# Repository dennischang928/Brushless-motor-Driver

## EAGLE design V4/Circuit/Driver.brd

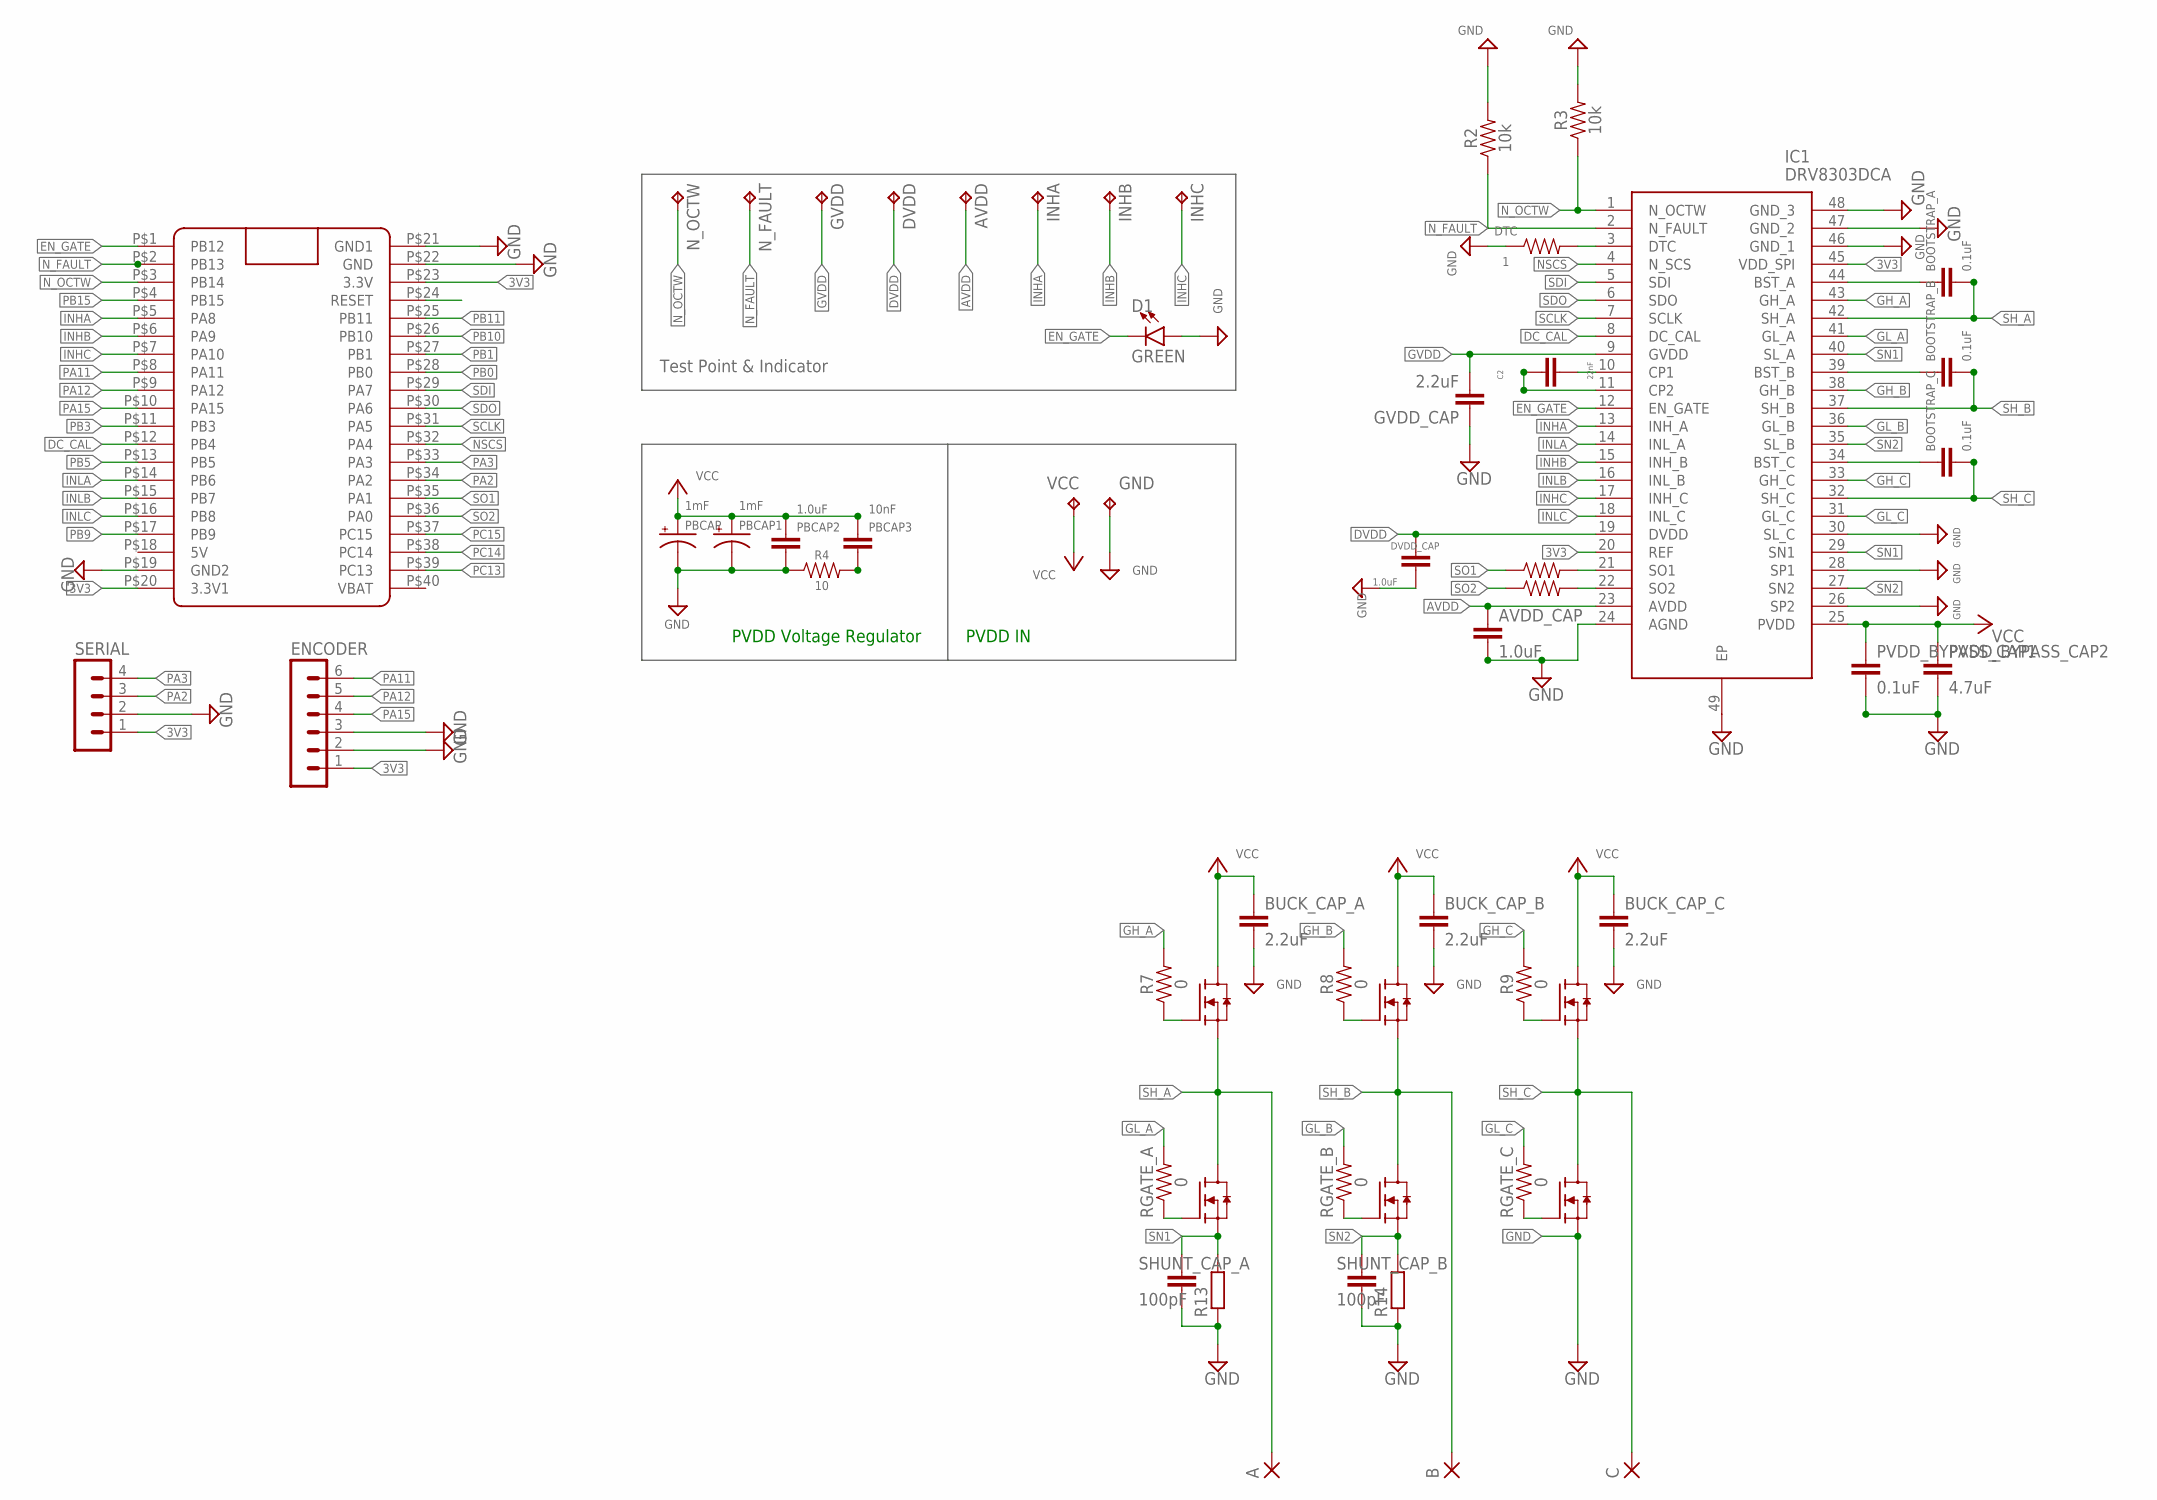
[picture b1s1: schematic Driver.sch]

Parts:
A: SMD5; SMD2,54-5,08
AVDD: TPTP16R; TP16R
AVDD_CAP: 1.0uF; 0603
B: SMD5; SMD2,54-5,08
BOOTSTRAP_A: 0.1uF; 0603
BOOTSTRAP_B: 0.1uF; 0603
BOOTSTRAP_C: 0.1uF; 0603
BUCK_CAP_A: 2.2uF; 0603
BUCK_CAP_B: 2.2uF; 0603
BUCK_CAP_C: 2.2uF; 0603
C: SMD5; SMD2,54-5,08
C2: 22nF; 0603
D1: GREEN; LED-0603
DTC: 1; 0603
DVDD: TPTP16R; TP16R
DVDD_CAP: 1.0uF; 0603
ENCODER: MA06-1
GND: TPPAD1-20Y; P1-20Y
GVDD: TPTP16R; TP16R
GVDD_CAP: 2.2uF; 0603
HA: IRLR7843; TO252
HB: IRLR7843; TO252
HC: IRLR7843; TO252
IC1: DRV8303DCA; SOP50P810X120-49N
INHA: TPTP16R; TP16R
INHB: TPTP16R; TP16R
INHC: TPTP16R; TP16R
LA: IRLR7843; TO252
LB: IRLR7843; TO252
LC: IRLR7843; TO252
N_FAULT: TPTP16R; TP16R
N_OCTW: TPTP16R; TP16R
PBCAP, PBCAP1: 1mF; CPOL-RADIAL-5MM-10MM
PBCAP2: 1.0uF; 0603
PBCAP3: 10nF; 0603
PVDD_BYPASS_CAP1: 0.1uF; 0603
PVDD_BYPASS_CAP2: 4.7uF; 0603
R2, R3: 10k; 0603
R4: 10; 0603
R5, R6: 47; 0603
R7, R8, R9: 0; 0603
R13, R14: R-EU_R2512; R2512
RGATE_A: 0; 0603
RGATE_B: 0; 0603
RGATE_C: 0; 0603
SERIAL: MA04-1
SHUNT_CAP_A: 100pF; 0603
SHUNT_CAP_B: 100pF; 0603
U$1: BLUE_PILLADVANCED; BLUE_PILL_ADV
VCC: TPPAD1-20Y; P1-20Y

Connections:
3V3: ENCODER.1, IC1.20 (REF), IC1.45 (VDD_SPI), SERIAL.1, U$1.P$20 (3.3V1), U$1.P$23 (3.3V)
AVDD: AVDD.TP, AVDD_CAP.1, IC1.23 (AVDD)
DC_CAL: IC1.8 (DC_CAL), U$1.P$12 (PB4)
DVDD: DVDD.TP, DVDD_CAP.1, IC1.19 (DVDD)
EN_GATE: D1.C, IC1.12 (EN_GATE), U$1.P$1 (PB12)
GH_A: IC1.43 (GH_A), R7.2
GH_B: IC1.38 (GH_B), R8.2
GH_C: IC1.33 (GH_C), R9.2
GL_A: IC1.41 (GL_A), RGATE_A.2
GL_B: IC1.36 (GL_B), RGATE_B.2
GL_C: IC1.31 (GL_C), RGATE_C.2
GND: AVDD_CAP.2, BUCK_CAP_A.2, BUCK_CAP_B.2, BUCK_CAP_C.2, D1.A, DTC.1, DVDD_CAP.2, ENCODER.2, ENCODER.3, GND.TP, GVDD_CAP.1, IC1.24 (AGND), IC1.26 (SP2), IC1.28 (SP1), IC1.30 (SL_C), IC1.46 (GND_1), IC1.47 (GND_2), IC1.48 (GND_3), IC1.49 (EP), LC.2 (S), PBCAP.-, PBCAP1.-, PBCAP2.2, PVDD_BYPASS_CAP1.2, PVDD_BYPASS_CAP2.2, R2.2, R3.2, R4.1, R13.1, R14.1, SERIAL.2, SHUNT_CAP_A.2, SHUNT_CAP_B.2, U$1.P$19 (GND2), U$1.P$21 (GND1), U$1.P$22 (GND)
GVDD: GVDD.TP, GVDD_CAP.2, IC1.9 (GVDD)
INHA: IC1.13 (INH_A), INHA.TP, U$1.P$5 (PA8)
INHB: IC1.15 (INH_B), INHB.TP, U$1.P$6 (PA9)
INHC: IC1.17 (INH_C), INHC.TP, U$1.P$7 (PA10)
INLA: IC1.14 (INL_A), U$1.P$14 (PB6)
INLB: IC1.16 (INL_B), U$1.P$15 (PB7)
INLC: IC1.18 (INL_C), U$1.P$16 (PB8)
unnamed: DTC.2, IC1.3 (DTC)
unnamed: PBCAP3.2, R4.2
unnamed: BOOTSTRAP_A.1, IC1.44 (BST_A)
unnamed: HA.1 (G), R7.1
unnamed: HB.1 (G), R8.1
unnamed: HC.1 (G), R9.1
unnamed: BOOTSTRAP_B.1, IC1.39 (BST_B)
unnamed: LC.1 (G), RGATE_C.1
unnamed: BOOTSTRAP_C.1, IC1.34 (BST_C)
unnamed: LB.1 (G), RGATE_B.1
unnamed: LA.1 (G), RGATE_A.1
unnamed: C2.2, IC1.10 (CP1)
unnamed: C2.1, IC1.11 (CP2)
NSCS: IC1.4 (N_SCS), U$1.P$32 (PA4)
N_FAULT: IC1.2 (N_FAULT), N_FAULT.TP, R2.1, U$1.P$2 (PB13)
N_OCTW: IC1.1 (N_OCTW), N_OCTW.TP, R3.1, U$1.P$3 (PB14)
PA2: SERIAL.3, U$1.P$34 (PA2)
PA3: SERIAL.4, U$1.P$33 (PA3)
PA11: ENCODER.6, U$1.P$8 (PA11)
PA12: ENCODER.5, U$1.P$9 (PA12)
PA15: ENCODER.4, U$1.P$10 (PA15)
PB0: U$1.P$28 (PB0)
PB1: U$1.P$27 (PB1)
PB3: U$1.P$11 (PB3)
PB5: U$1.P$13 (PB5)
PB9: U$1.P$17 (PB9)
PB10: U$1.P$26 (PB10)
PB11: U$1.P$25 (PB11)
PB15: U$1.P$4 (PB15)
PC13: U$1.P$39 (PC13)
PC14: U$1.P$38 (PC14)
PC15: U$1.P$37 (PC15)
SCLK: IC1.7 (SCLK), U$1.P$31 (PA5)
SDI: IC1.5 (SDI), U$1.P$29 (PA7)
SDO: IC1.6 (SDO), U$1.P$30 (PA6)
SH_A: A.1, BOOTSTRAP_A.2, HA.2 (S), IC1.42 (SH_A), LA.3 (D)
SH_B: B.1, BOOTSTRAP_B.2, HB.2 (S), IC1.37 (SH_B), LB.3 (D)
SH_C: BOOTSTRAP_C.2, C.1, HC.2 (S), IC1.32 (SH_C), LC.3 (D)
SN1: IC1.29 (SN1), IC1.40 (SL_A), LA.2 (S), R13.2, SHUNT_CAP_A.1
SN2: IC1.27 (SN2), IC1.35 (SL_B), LB.2 (S), R14.2, SHUNT_CAP_B.1
SO1: R5.1, U$1.P$35 (PA1)
SO1B: IC1.21 (SO1), R5.2
SO2: R6.1, U$1.P$36 (PA0)
SO2B: IC1.22 (SO2), R6.2
VCC: BUCK_CAP_A.1, BUCK_CAP_B.1, BUCK_CAP_C.1, HA.3 (D), HB.3 (D), HC.3 (D), IC1.25 (PVDD), PBCAP.+, PBCAP1.+, PBCAP2.1, PBCAP3.1, PVDD_BYPASS_CAP1.1, PVDD_BYPASS_CAP2.1, VCC.TP

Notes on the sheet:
Test Point & Indicator
PVDD Voltage Regulator
PVDD IN

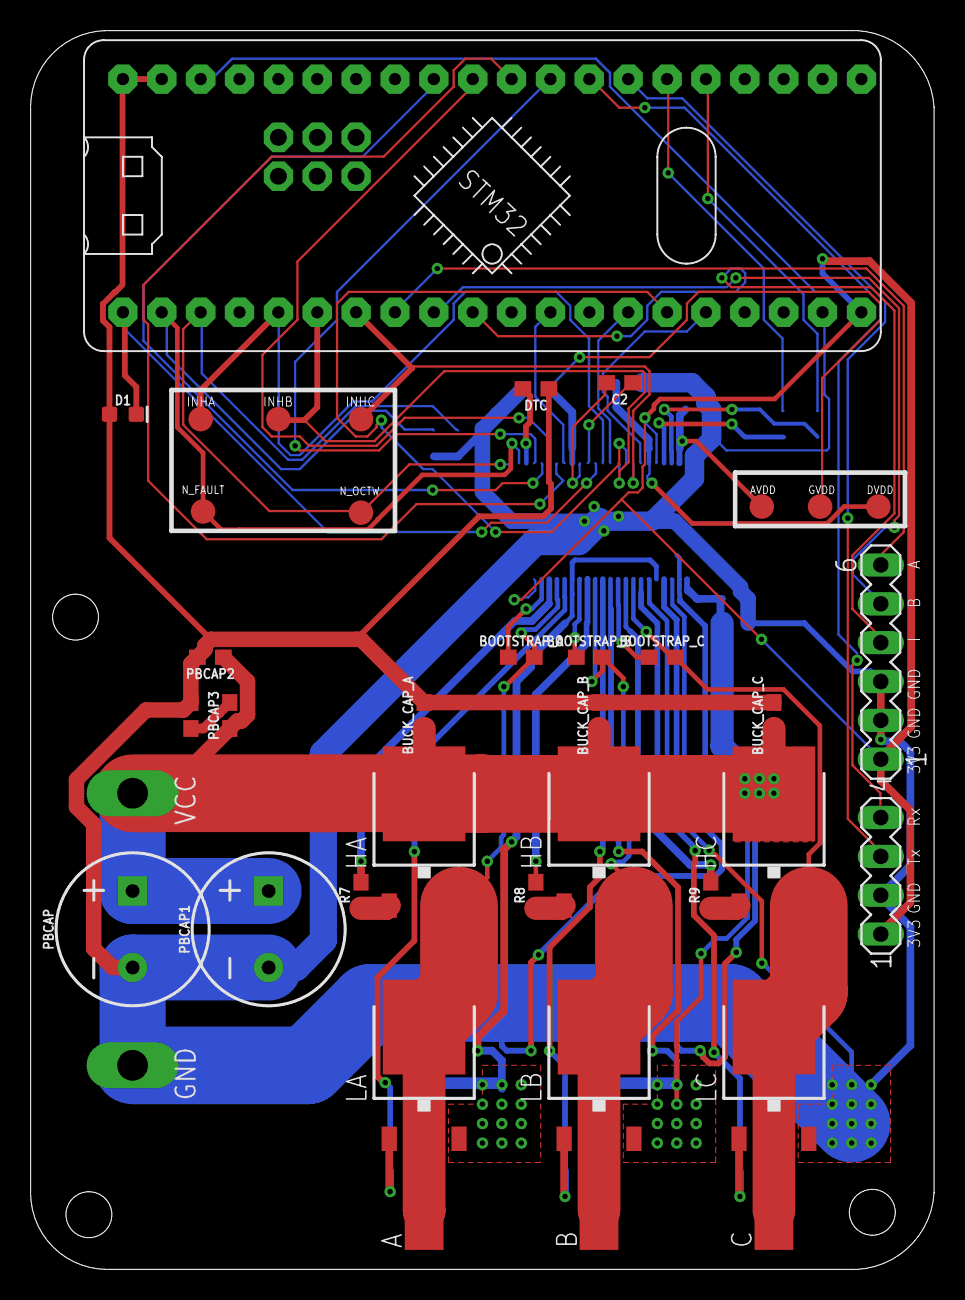
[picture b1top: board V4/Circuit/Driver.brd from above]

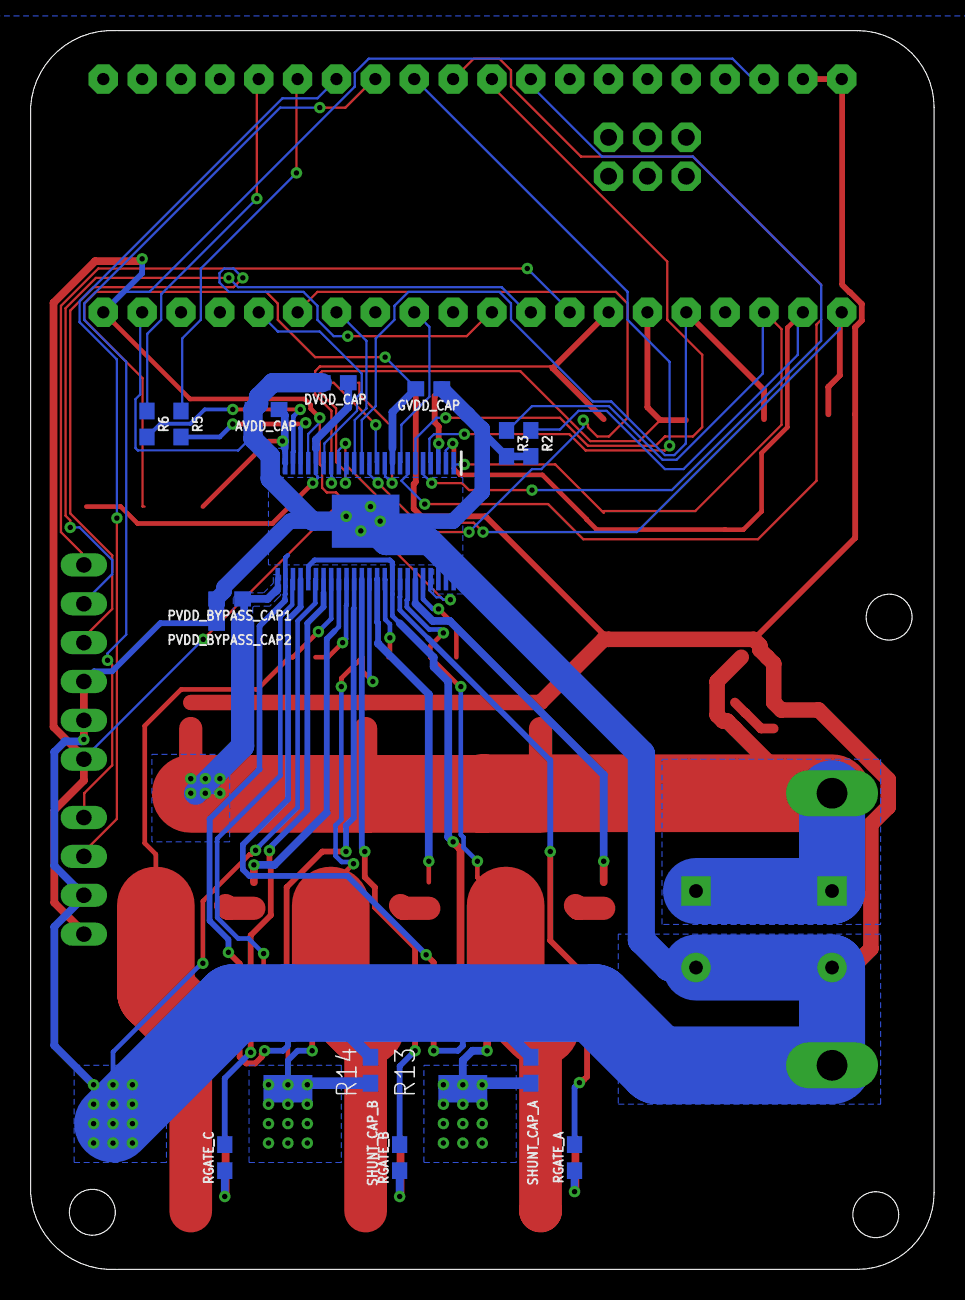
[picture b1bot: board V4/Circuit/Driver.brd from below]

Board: 2 copper layers, 59.0 x 81.0 mm, 56 parts (17 on the bottom side), 53 nets.

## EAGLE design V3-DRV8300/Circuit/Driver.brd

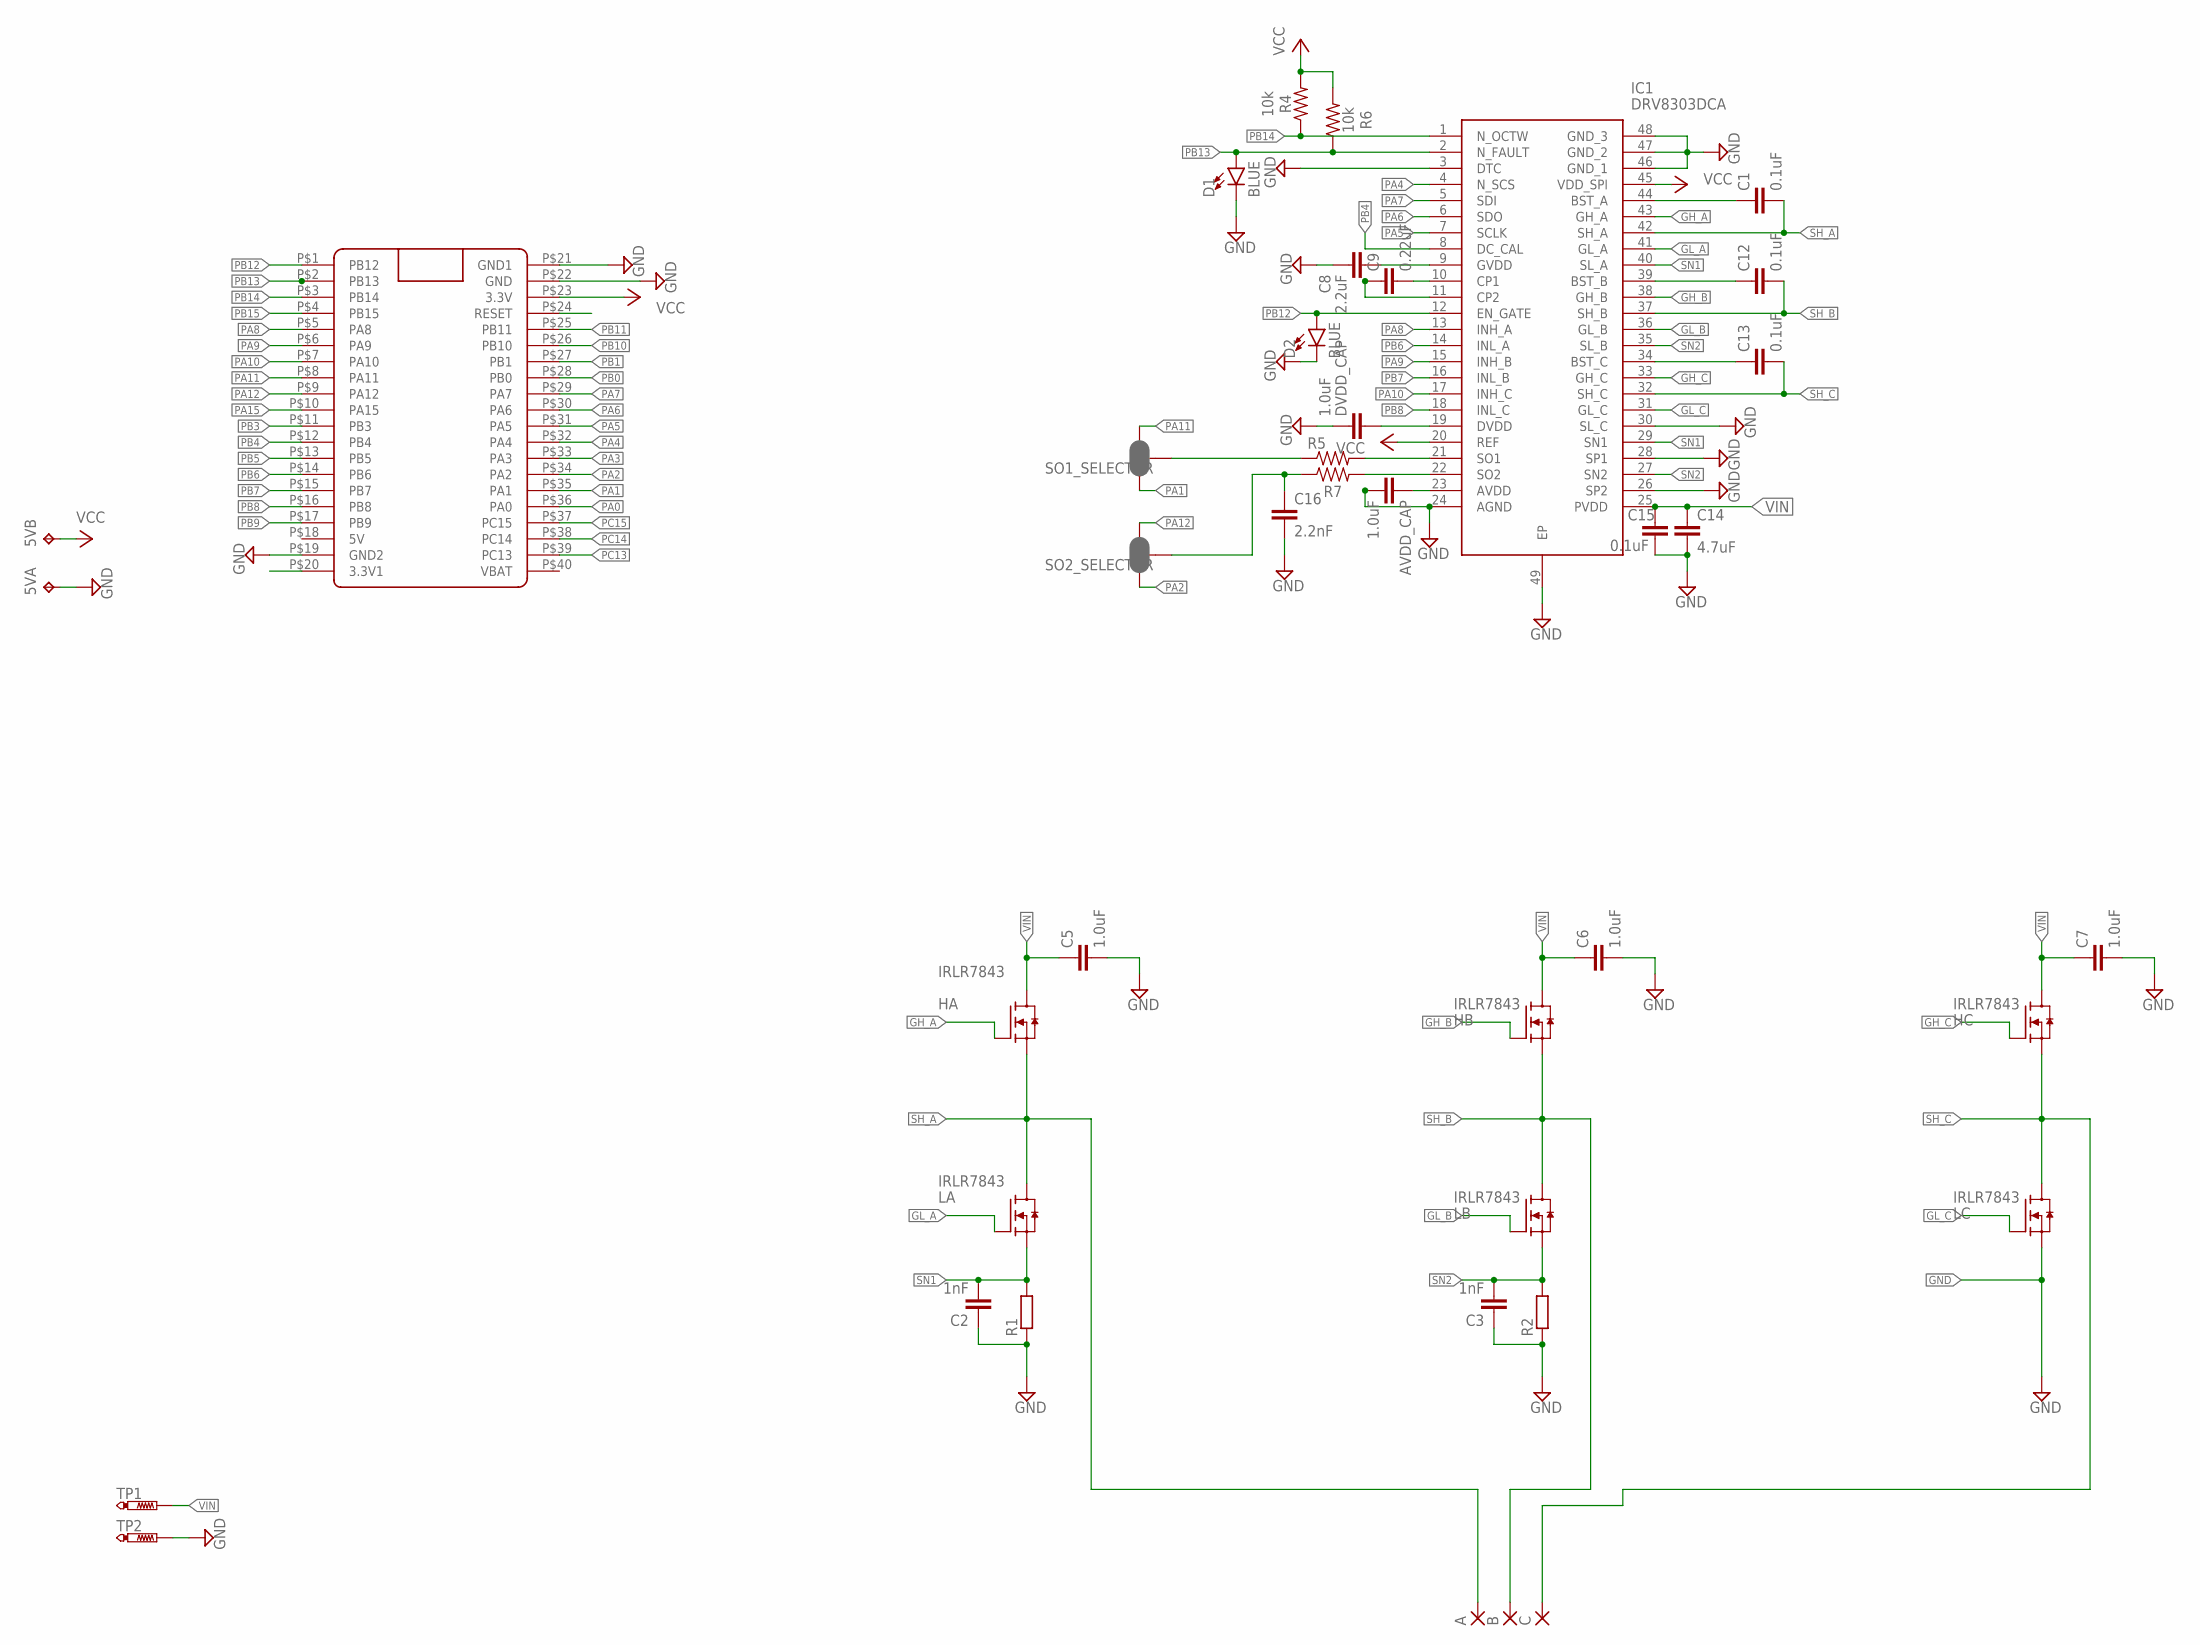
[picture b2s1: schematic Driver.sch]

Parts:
5V: TP2P2-38-17; P2-38-17
A: SMD5; SMD2,54-5,08
AVDD_CAP: 1.0uF; 0603
B: SMD5; SMD2,54-5,08
C: SMD5; SMD2,54-5,08
C1, C12, C13, C15: 0.1uF; 0603
C2, C3: 1nF; 0603
C5, C6, C7: 1.0uF; 0603
C8: 2.2uF; 0603
C9: 0.22uF; 0603
C14: 4.7uF; 0603
C16: 2.2nF; 0603
D1, D2: BLUE; LED-0603
DVDD_CAP: 1.0uF; 0603
HA: IRLR7843; TO252
HB: IRLR7843; TO252
HC: IRLR7843; TO252
IC1: DRV8303DCA; SOP50P810X120-49N
LA: IRLR7843; TO252
LB: IRLR7843; TO252
LC: IRLR7843; TO252
R1, R2: R-EU_R2512; R2512
R4, R6: 10k; 0603
R5, R7: 0; 0603
SO1_SELECTOR, SO2_SELECTOR: JUMPER-SMT_3_2-NC_PASTE_SILK; SMT-JUMPER_3_2-NC_PASTE_SILK
TP1, TP2: PTR1PAD1-20Y; P1-20Y
U$1: BLUE_PILLADVANCED; BLUE_PILL_ADV

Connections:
GH_A: HA.1 (G), IC1.43 (GH_A)
GH_B: HB.1 (G), IC1.38 (GH_B)
GH_C: HC.1 (G), IC1.33 (GH_C)
GL_A: IC1.41 (GL_A), LA.1 (G)
GL_B: IC1.36 (GL_B), LB.1 (G)
GL_C: IC1.31 (GL_C), LC.1 (G)
GND: 5V.TP-1, AVDD_CAP.2, C2.1, C3.1, C5.2, C6.2, C7.2, C8.2, C14.2, C15.2, C16.2, D1.C, D2.C, DVDD_CAP.1, IC1.3 (DTC), IC1.24 (AGND), IC1.26 (SP2), IC1.28 (SP1), IC1.30 (SL_C), IC1.46 (GND_1), IC1.47 (GND_2), IC1.48 (GND_3), IC1.49 (EP), LC.2 (S), R1.1, R2.1, TP2.TP, U$1.P$19 (GND2), U$1.P$21 (GND1), U$1.P$22 (GND)
unnamed: IC1.21 (SO1), R5.2
unnamed: C1.1, IC1.44 (BST_A)
unnamed: IC1.22 (SO2), R7.2
unnamed: C12.1, IC1.39 (BST_B)
unnamed: C13.1, IC1.34 (BST_C)
unnamed: C8.1, IC1.9 (GVDD)
unnamed: C9.2, IC1.10 (CP1)
unnamed: C9.1, IC1.11 (CP2)
unnamed: DVDD_CAP.2, IC1.19 (DVDD)
unnamed: AVDD_CAP.1, IC1.23 (AVDD)
PA0: U$1.P$36 (PA0)
PA1: SO1_SELECTOR.1, U$1.P$35 (PA1)
PA2: SO2_SELECTOR.1, U$1.P$34 (PA2)
PA3: U$1.P$33 (PA3)
PA4: IC1.4 (N_SCS), U$1.P$32 (PA4)
PA5: IC1.7 (SCLK), U$1.P$31 (PA5)
PA6: IC1.6 (SDO), U$1.P$30 (PA6)
PA7: IC1.5 (SDI), U$1.P$29 (PA7)
PA8: IC1.13 (INH_A), U$1.P$5 (PA8)
PA9: IC1.15 (INH_B), U$1.P$6 (PA9)
PA10: IC1.17 (INH_C), U$1.P$7 (PA10)
PA11: SO1_SELECTOR.3, U$1.P$8 (PA11)
PA12: SO2_SELECTOR.3, U$1.P$9 (PA12)
PA15: U$1.P$10 (PA15)
PB0: U$1.P$28 (PB0)
PB1: U$1.P$27 (PB1)
PB3: U$1.P$11 (PB3)
PB4: IC1.8 (DC_CAL), U$1.P$12 (PB4)
PB5: U$1.P$13 (PB5)
PB6: IC1.14 (INL_A), U$1.P$14 (PB6)
PB7: IC1.16 (INL_B), U$1.P$15 (PB7)
PB8: IC1.18 (INL_C), U$1.P$16 (PB8)
PB9: U$1.P$17 (PB9)
PB10: U$1.P$26 (PB10)
PB11: U$1.P$25 (PB11)
PB12: D2.A, IC1.12 (EN_GATE), U$1.P$1 (PB12)
PB13: D1.A, IC1.2 (N_FAULT), R6.1, U$1.P$2 (PB13)
PB14: IC1.1 (N_OCTW), R4.1, U$1.P$3 (PB14)
PB15: U$1.P$4 (PB15)
PC13: U$1.P$39 (PC13)
PC14: U$1.P$38 (PC14)
PC15: U$1.P$37 (PC15)
SH_A: A.1, C1.2, HA.2 (S), IC1.42 (SH_A), LA.3 (D)
SH_B: B.1, C12.2, HB.2 (S), IC1.37 (SH_B), LB.3 (D)
SH_C: C.1, C13.2, HC.2 (S), IC1.32 (SH_C), LC.3 (D)
SN1: C2.2, IC1.29 (SN1), IC1.40 (SL_A), LA.2 (S), R1.2
SN2: C3.2, IC1.27 (SN2), IC1.35 (SL_B), LB.2 (S), R2.2
SO1: R5.1, SO1_SELECTOR.2
SO2: C16.1, R7.1, SO2_SELECTOR.2
VCC: 5V.TP-2, IC1.20 (REF), IC1.45 (VDD_SPI), R4.2, R6.2, U$1.P$23 (3.3V)
VIN: C5.1, C6.1, C7.1, C14.1, C15.1, HA.3 (D), HB.3 (D), HC.3 (D), IC1.25 (PVDD), TP1.TP

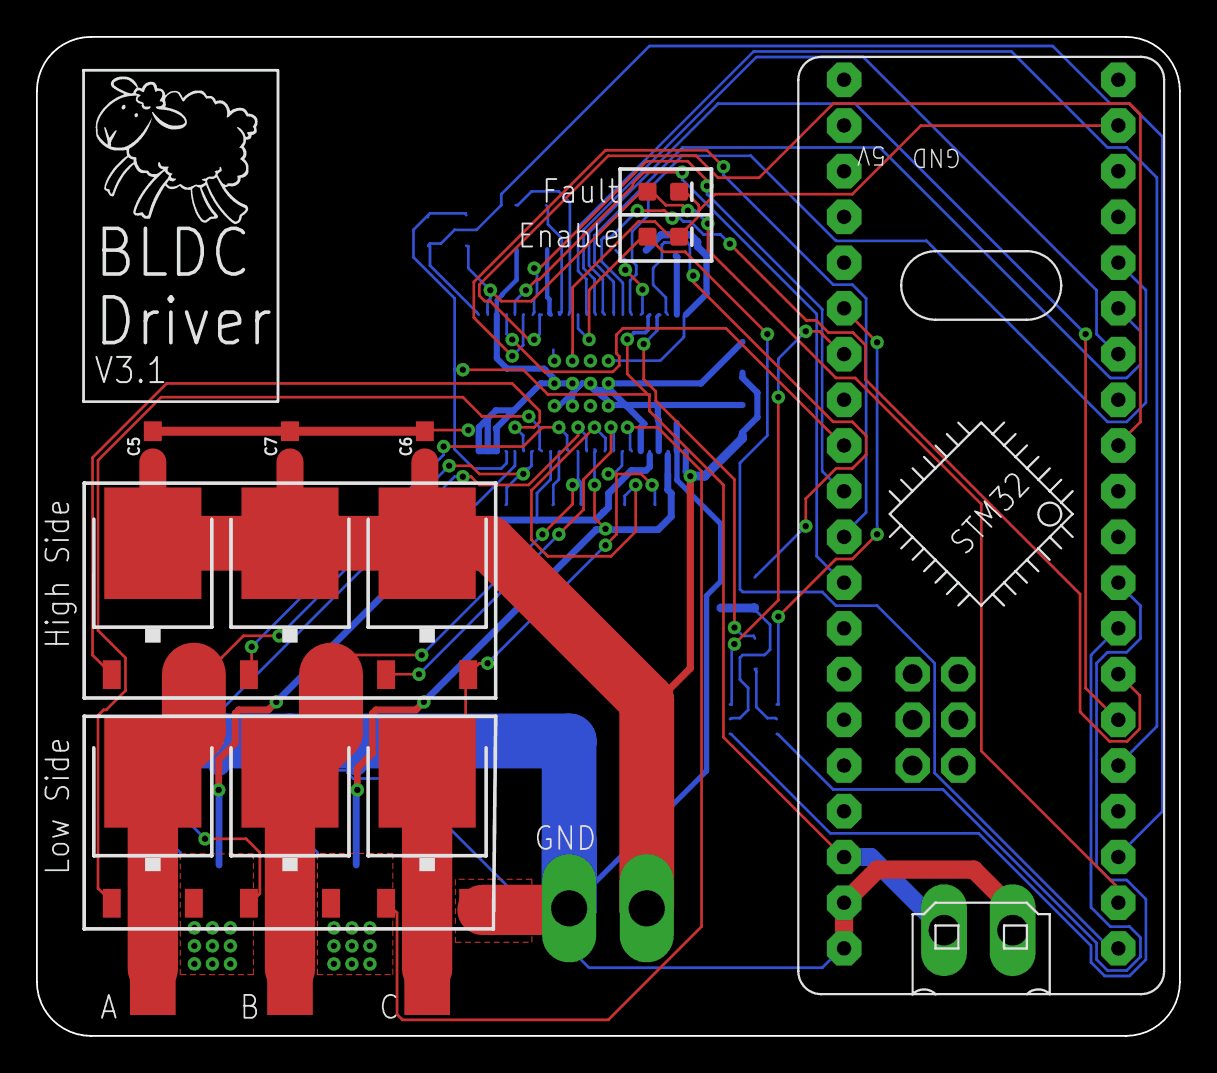
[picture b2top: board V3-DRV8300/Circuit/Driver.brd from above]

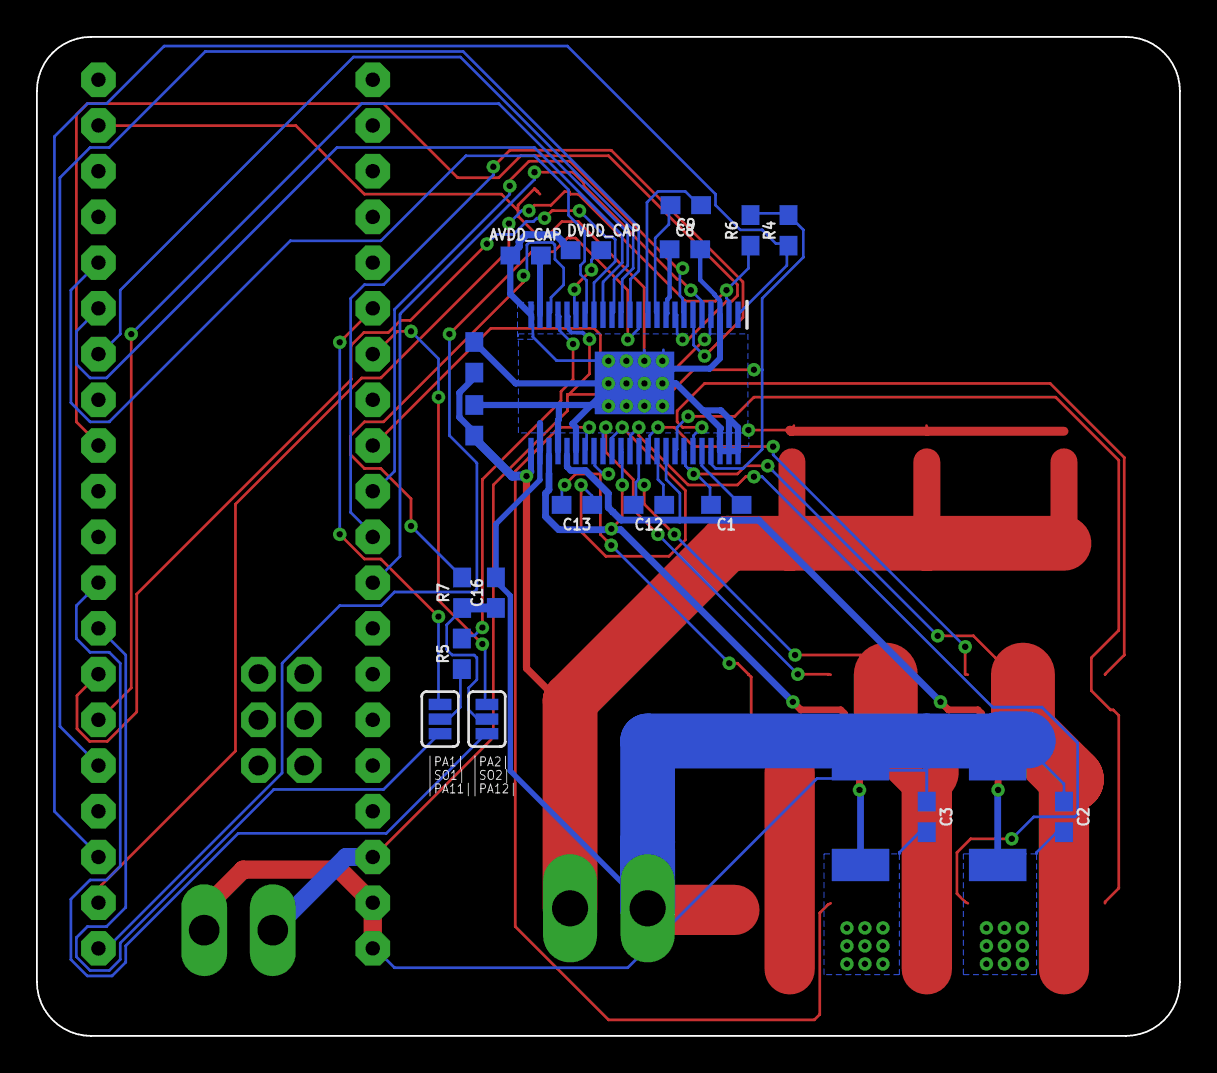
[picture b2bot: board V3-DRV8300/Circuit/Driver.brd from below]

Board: 2 copper layers, 63.5 x 55.5 mm, 39 parts (21 on the bottom side), 44 nets.

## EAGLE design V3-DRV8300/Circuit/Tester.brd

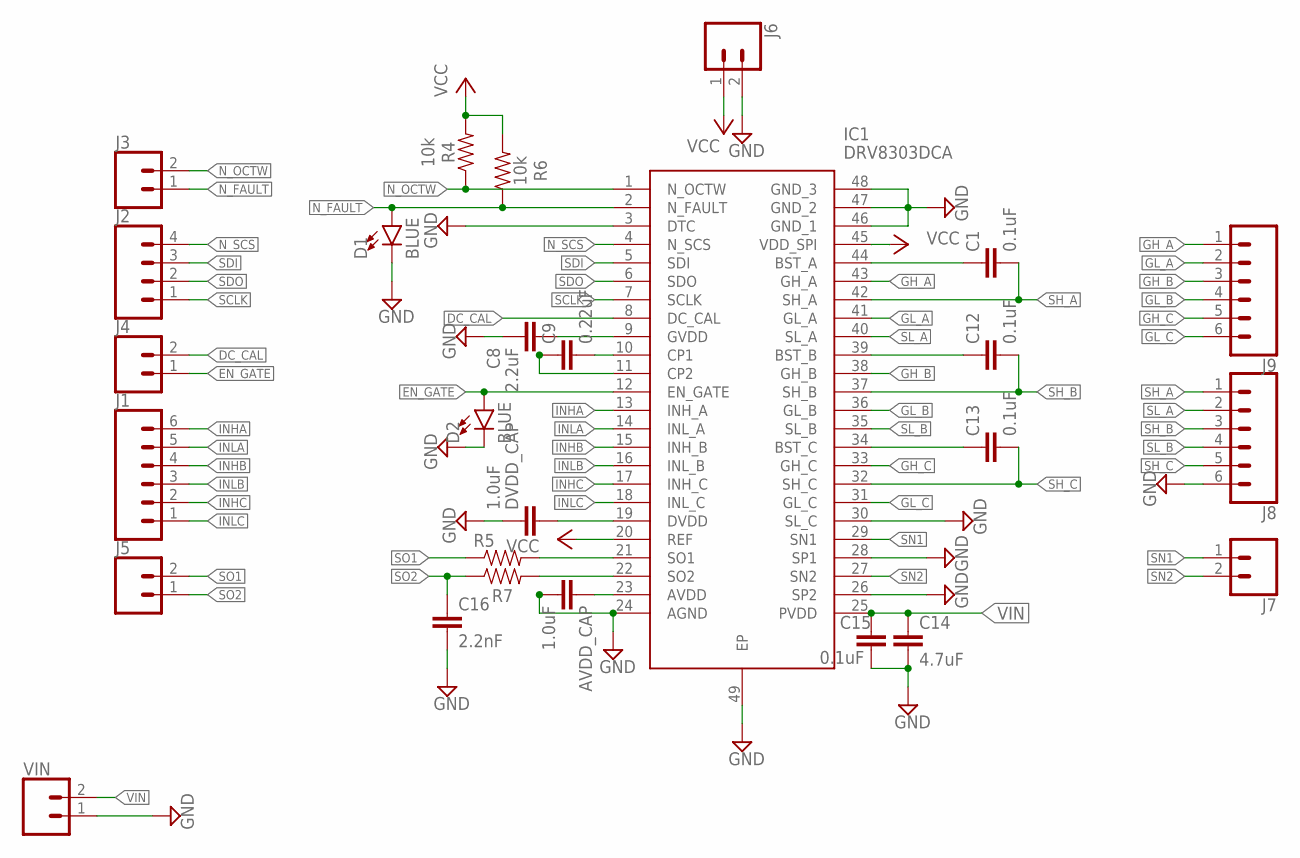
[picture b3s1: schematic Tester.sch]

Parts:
AVDD_CAP: 1.0uF; 0603
C1, C12, C13, C15: 0.1uF; 0603
C8: 2.2uF; 0603
C9: 0.22uF; 0603
C14: 4.7uF; 0603
C16: 2.2nF; 0603
D1, D2: BLUE; LED-0603
DVDD_CAP: 1.0uF; 0603
IC1: DRV8303DCA; SOP50P810X120-49N
J1, J8, J9: CONN_06SILK_FEMALE_PTH; 1X06
J2: CONN_04PTH; 1X04
J3, J4, J5, J6, J7: CONN_02; 1X02
R4, R6: 10k; 0603
R5, R7: 0; 0603
VIN: CONN_02LOCK_LONGPADS; 1X02_LOCK_LONGPADS

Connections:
DC_CAL: IC1.8 (DC_CAL), J4.2
EN_GATE: D2.A, IC1.12 (EN_GATE), J4.1
GH_A: IC1.43 (GH_A), J9.1
GH_B: IC1.38 (GH_B), J9.3
GH_C: IC1.33 (GH_C), J9.5
GL_A: IC1.41 (GL_A), J9.2
GL_B: IC1.36 (GL_B), J9.4
GL_C: IC1.31 (GL_C), J9.6
GND: AVDD_CAP.2, C8.2, C14.2, C15.2, C16.2, D1.C, D2.C, DVDD_CAP.1, IC1.3 (DTC), IC1.24 (AGND), IC1.26 (SP2), IC1.28 (SP1), IC1.30 (SL_C), IC1.46 (GND_1), IC1.47 (GND_2), IC1.48 (GND_3), IC1.49 (EP), J6.2, J8.6, VIN.1
INHA: IC1.13 (INH_A), J1.6
INHB: IC1.15 (INH_B), J1.4
INHC: IC1.17 (INH_C), J1.2
INLA: IC1.14 (INL_A), J1.5
INLB: IC1.16 (INL_B), J1.3
INLC: IC1.18 (INL_C), J1.1
unnamed: IC1.21 (SO1), R5.2
unnamed: C1.1, IC1.44 (BST_A)
unnamed: IC1.22 (SO2), R7.2
unnamed: C12.1, IC1.39 (BST_B)
unnamed: C13.1, IC1.34 (BST_C)
unnamed: C8.1, IC1.9 (GVDD)
unnamed: C9.2, IC1.10 (CP1)
unnamed: C9.1, IC1.11 (CP2)
unnamed: DVDD_CAP.2, IC1.19 (DVDD)
unnamed: AVDD_CAP.1, IC1.23 (AVDD)
N_FAULT: D1.A, IC1.2 (N_FAULT), J3.1, R6.1
N_OCTW: IC1.1 (N_OCTW), J3.2, R4.1
N_SCS: IC1.4 (N_SCS), J2.4
SCLK: IC1.7 (SCLK), J2.1
SDI: IC1.5 (SDI), J2.3
SDO: IC1.6 (SDO), J2.2
SH_A: C1.2, IC1.42 (SH_A), J8.1
SH_B: C12.2, IC1.37 (SH_B), J8.3
SH_C: C13.2, IC1.32 (SH_C), J8.5
SL_A: IC1.40 (SL_A), J8.2
SL_B: IC1.35 (SL_B), J8.4
SN1: IC1.29 (SN1), J7.1
SN2: IC1.27 (SN2), J7.2
SO1: J5.2, R5.1
SO2: C16.1, J5.1, R7.1
VCC: IC1.20 (REF), IC1.45 (VDD_SPI), J6.1, R4.2, R6.2
VIN: C14.1, C15.1, IC1.25 (PVDD), VIN.2

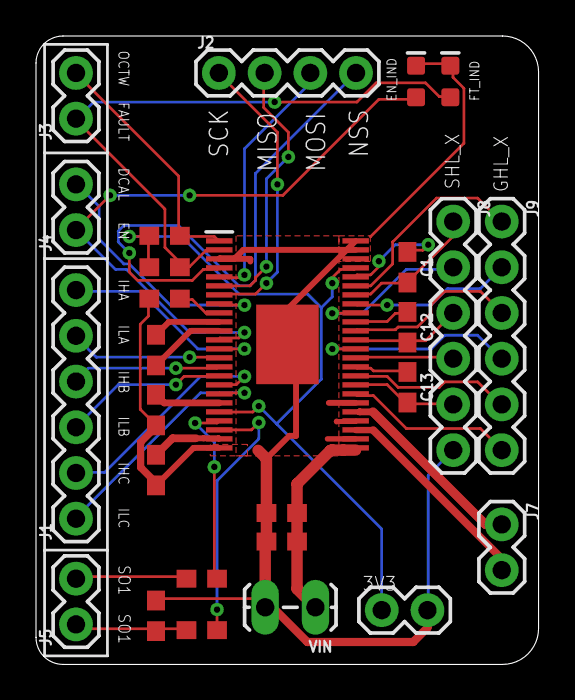
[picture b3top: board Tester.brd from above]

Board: 2 copper layers, 27.9 x 34.9 mm, 27 parts (0 on the bottom side), 42 nets.

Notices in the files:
parts and their libraries:
SparkFun-Capacitors: Licensing: Creative Commons ShareAlike 4.0 International - https://creativecommons.org/licenses/by-sa/4.0
